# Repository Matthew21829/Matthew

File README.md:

# buñuelo
## buñuelo first session 2 - [1 hour]
What i did: I downloaded the programs and then configured everything as shown in the tutorial. I wanted to create a schematic for four buttons and four LEDs.
Once the program was open, I imported the XIAO-RP2024 chip and placed it in my schematic. After that, I added the four buttons and then imported the LEDs, adding four of them and connecting a resistor to each
When that was ready, I connected them to the chip using the global tags and then connected them to ground. And that's how the schematic turned out.

# buñuelo second session - [1 hour]
What i did: In this second session, I imported the schematic into the PCB editor. Once I had the elements from my schematic, I started organizing and arranging them to my liking to begin connecting them.
After that, I checked for any errors and then viewed them in the 3D model. Following this, I imported the 3D models of the components (buttons, LEDs, and the chip) and arranged them until everything was correctly positioned. 
Finally, I put the name of my PCB, and that was it.

## pcb editor

## 3D model

# buñuelo third session [30 minutes]

After serveral minutes downloading Arduino IDE, i saw the tutorial and i changed things that i wanted from the code. 
This part was a little bit difficult for me, but i kept going as best i could, adjusting things to my liking. After finishing the code, i saved the project.

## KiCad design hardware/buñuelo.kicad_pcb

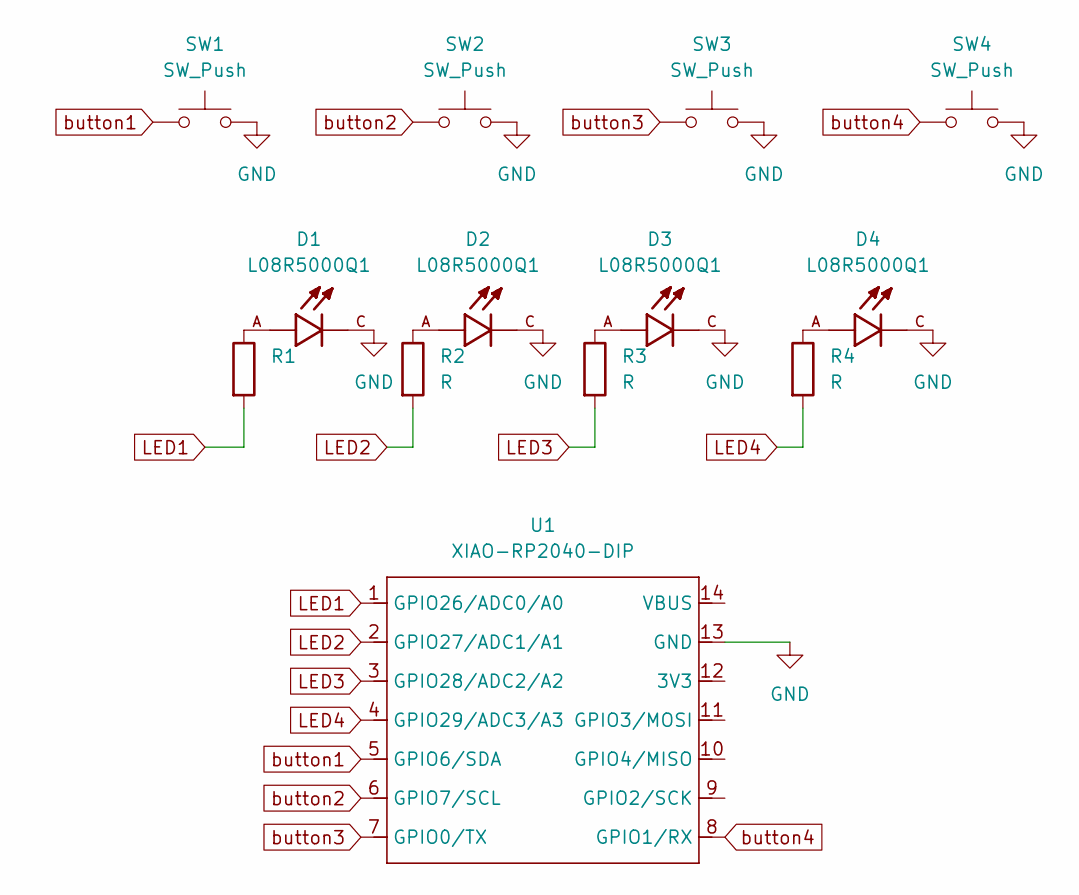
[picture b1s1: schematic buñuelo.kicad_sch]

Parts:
D1, D2, D3, D4: L08R5000Q1; LEDRD254W57D500H1070; PARTREV NA
R1, R2, R3, R4: R
SW1, SW2, SW3, SW4: SW_Push
U1: XIAO-RP2040-DIP; MOUDLE14P-XIAO-DIP-SMD

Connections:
GND: D1.C, D2.C, D3.C, D4.C, SW1.2, SW2.2, SW3.2, SW4.2, U1.13 (GND)
LED1: R1.2, U1.1 (GPIO26/ADC0/A0)
LED2: R2.2, U1.2 (GPIO27/ADC1/A1)
LED3: R3.2, U1.3 (GPIO28/ADC2/A2)
LED4: R4.2, U1.4 (GPIO29/ADC3/A3)
unnamed: D1.A, R1.1
unnamed: D2.A, R2.1
unnamed: D3.A, R3.1
unnamed: D4.A, R4.1
button1: SW1.1, U1.5 (GPIO6/SDA)
button2: SW2.1, U1.6 (GPIO7/SCL)
button3: SW3.1, U1.7 (GPIO0/TX)
button4: SW4.1, U1.8 (GPIO1/RX)

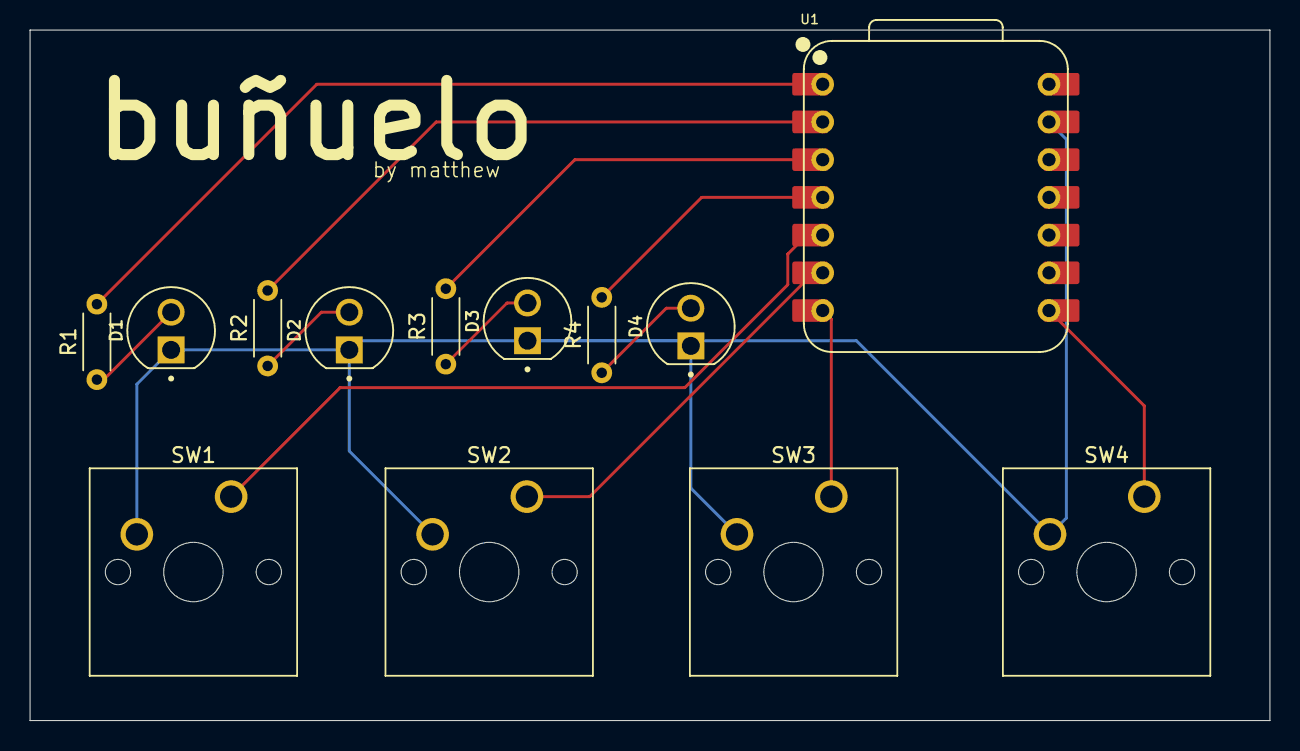
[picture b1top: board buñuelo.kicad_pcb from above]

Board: 2 copper layers, 83.5 x 46.5 mm, 13 parts (0 on the bottom side), 13 nets.

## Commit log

2025-10-29 hice la esquematica
2025-10-30 Create README.md
    scuematic
2025-10-30 hice el pcb
2025-11-01 finished project
2025-11-01 finished
